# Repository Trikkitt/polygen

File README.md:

The folders are as follows:

3D Models : Contains the STL files for the casing and information about the physical assembly
  
PIC : Contains the source code and compiled .HEX file for the PIC Microcontroller used by the game

Micropython : Contains the Micropyhon code used by the ESP8285 used by the game

PCB : Contains the KiCAD PCB design used in each of the game units
  
Game : Contains the primary game code including database

Sounds: The audio files played by the game units, along with some source / raw media.

The 3D model was designed using Tinkercad.  The URL for the 2024 design is https://www.tinkercad.com/things/fUl2xMWVo1S-polygen-case-2024-final and the 2025 design https://www.tinkercad.com/things/fGMrmOF5N9D-polygen-case-2025-final and this repository contains the export STL files from Tinkercad.

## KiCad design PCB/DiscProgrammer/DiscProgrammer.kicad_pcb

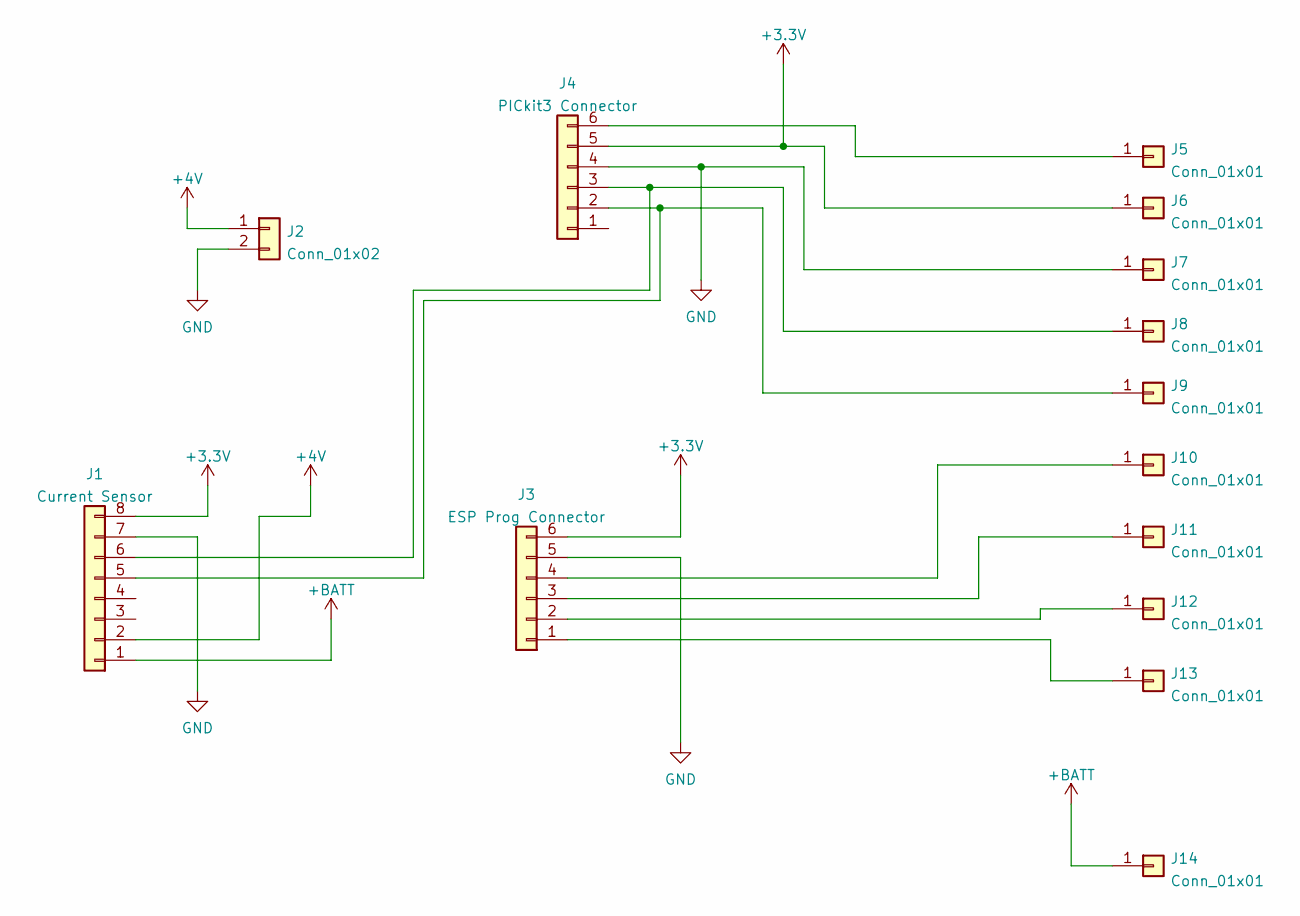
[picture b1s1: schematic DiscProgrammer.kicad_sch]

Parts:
J1: Current Sensor; PinHeader_1x08_P2.54mm_Vertical
J2: Conn_01x02; JST_PH_B2B-PH-K_1x02_P2.00mm_Vertical
J3: ESP Prog Connector; PinHeader_1x06_P2.54mm_Vertical
J4: PICkit3 Connector; PinHeader_1x06_P2.54mm_Vertical
J5, J6, J7, J8, J9, J10, J11, J12, J13, J14: Conn_01x01; Pin_D1.0mm_L10.0mm

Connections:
+3V3: J1.8, J3.6, J4.5, J6.1
+4V: J1.2, J2.1
+BATT: J1.1, J14.1
GND: J1.7, J2.2, J3.5, J4.4, J7.1
unnamed: J1.5, J4.2, J9.1
unnamed: J1.6, J4.3, J8.1
unnamed: J4.6, J5.1
unnamed: J3.4, J10.1
unnamed: J3.3, J11.1
unnamed: J3.2, J12.1
unnamed: J3.1, J13.1

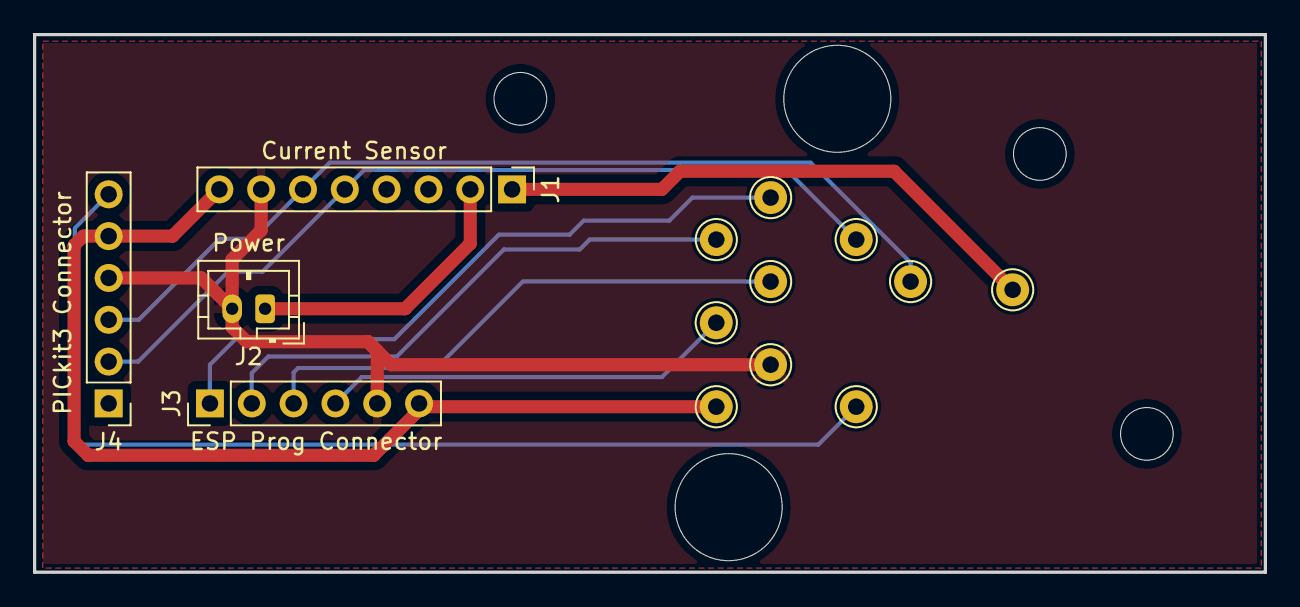
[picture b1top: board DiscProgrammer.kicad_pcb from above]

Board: 2 copper layers, 74.8 x 32.6 mm, 17 parts (0 on the bottom side), 11 nets.

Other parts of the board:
H1, H1#2: Orientation Guide 2; MountingHole_3.2mm_M3_DIN965
H2: Orientation Guide 1; MountingHole_3.2mm_M3_DIN965

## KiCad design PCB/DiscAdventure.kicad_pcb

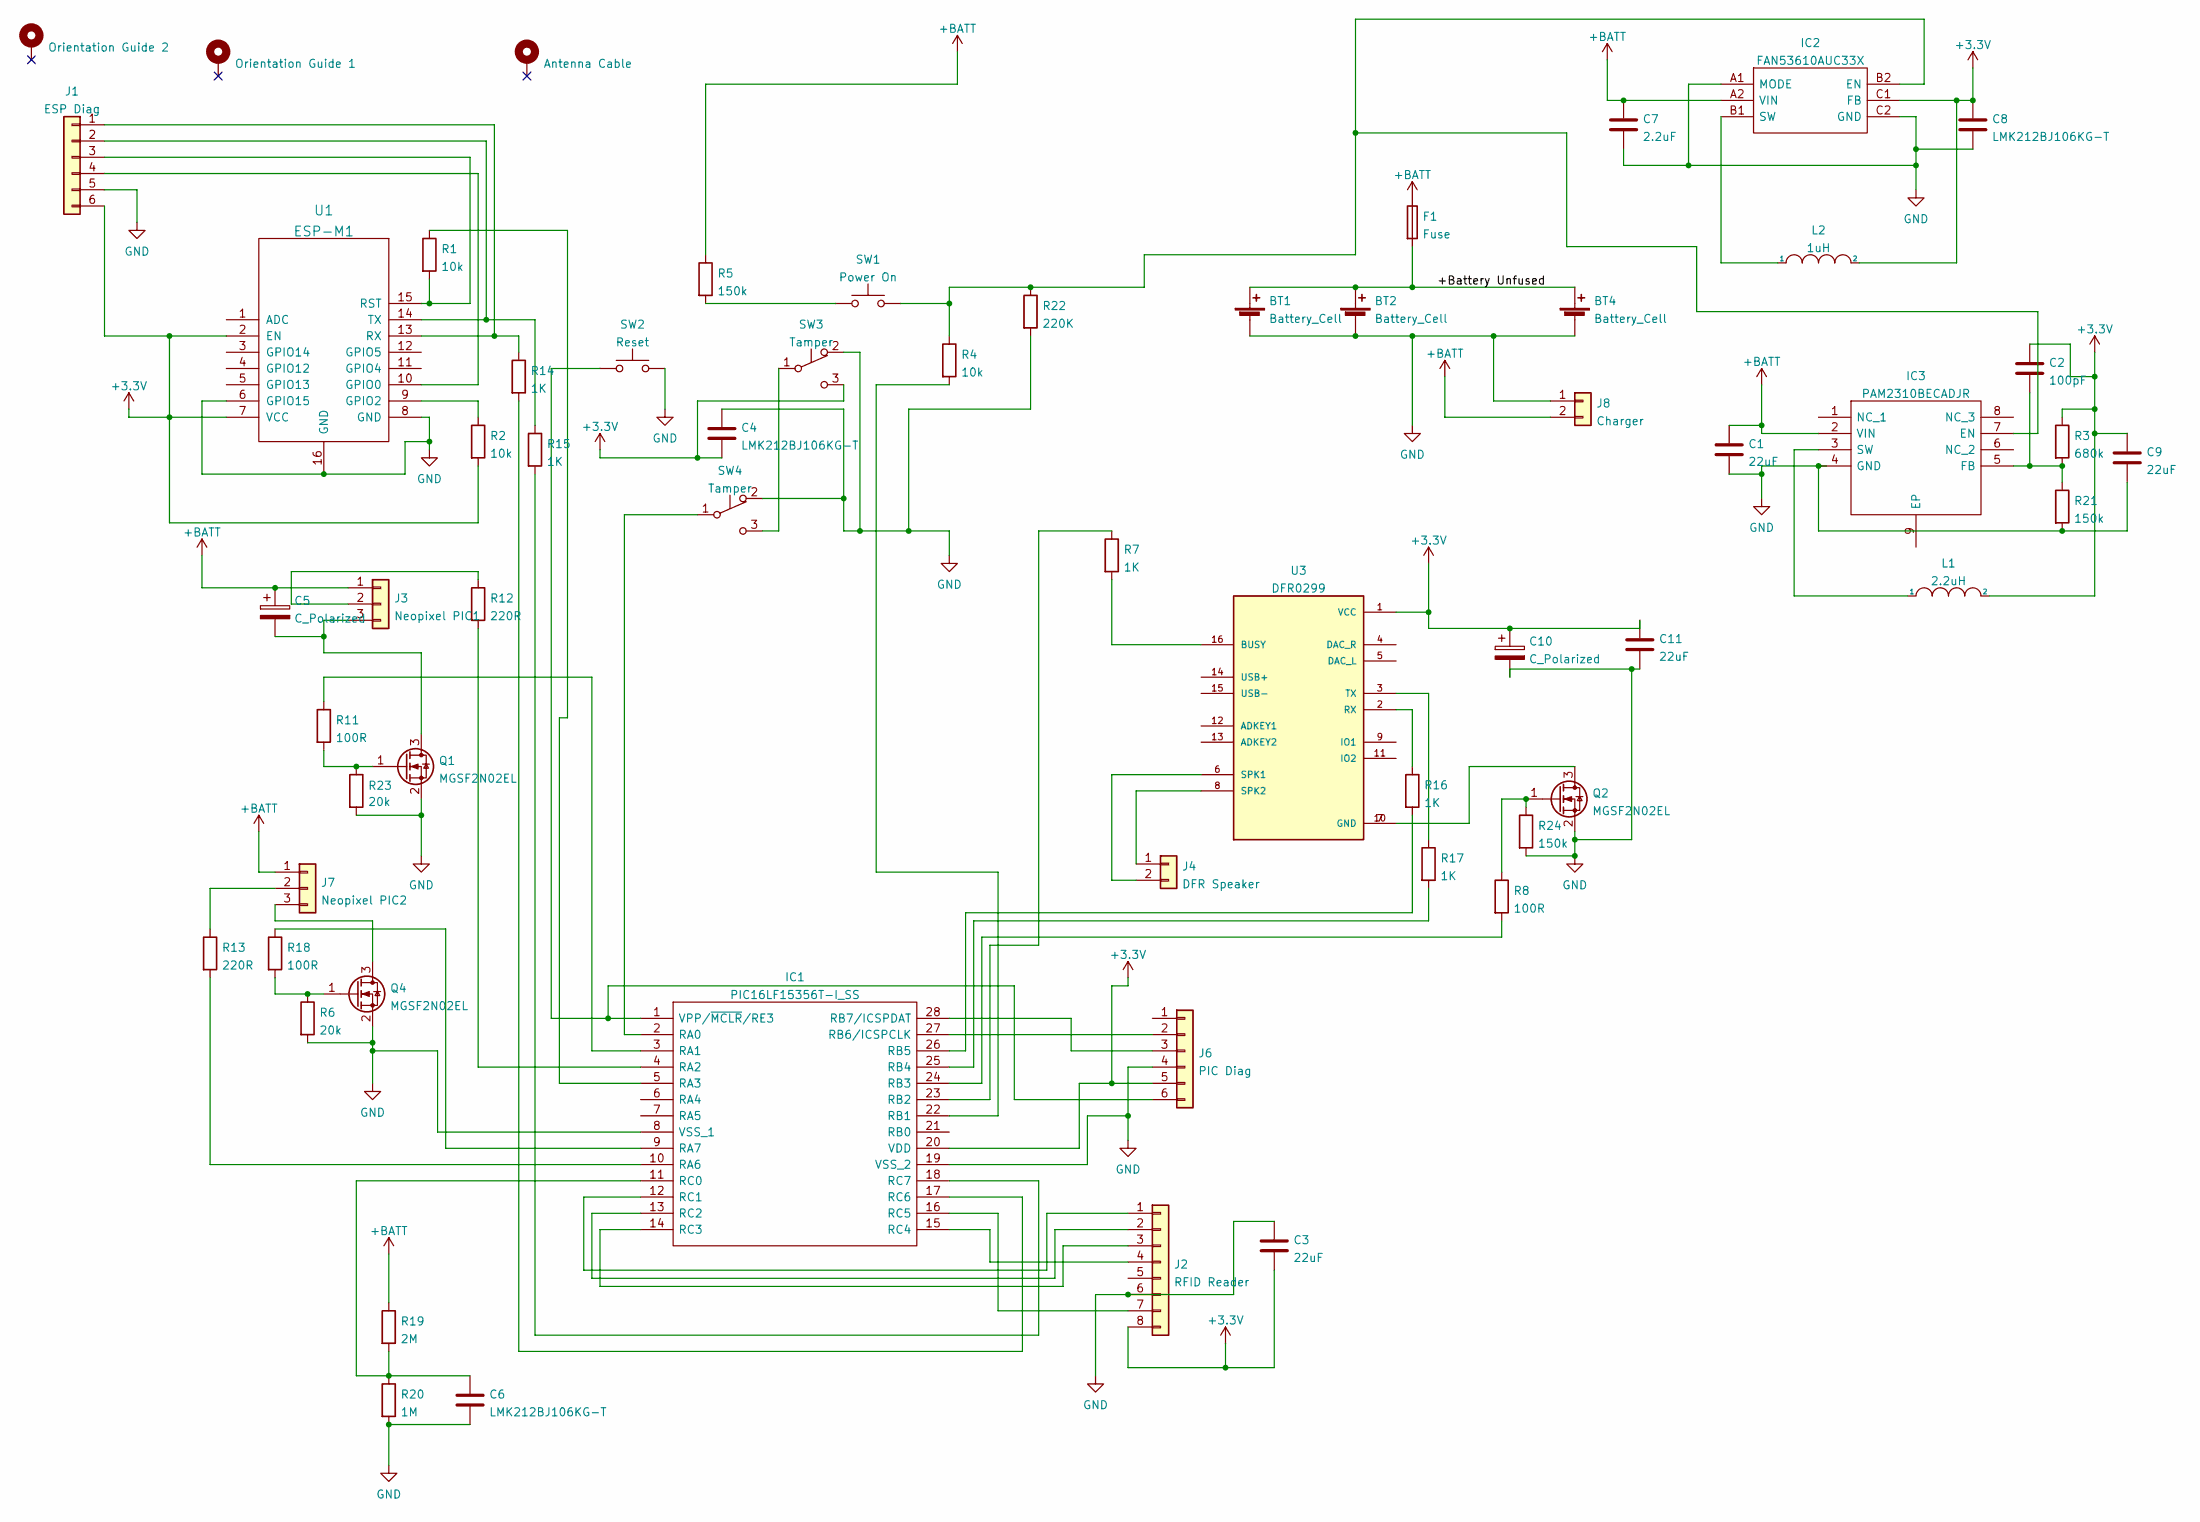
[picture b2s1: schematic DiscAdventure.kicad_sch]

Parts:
BT1, BT2, BT4: Battery_Cell; BatteryHolder_1x18650_TH
C1, C3, C9, C11: 22uF; C_0805_2012Metric
C2: 100pF; C_0805_2012Metric
C4, C6, C8: LMK212BJ106KG-T; C_0805_2012Metric
C5, C10: C_Polarized; CP_Radial_D8.0mm_P3.80mm
C7: 2.2uF; C_0805_2012Metric
F1: Fuse; Fuse_0603_1608Metric
H1: Orientation Guide 2; MountingHole_3.2mm_M3_DIN965
H2: Orientation Guide 1; MountingHole_3.2mm_M3_DIN965
H3: Antenna Cable; MountingHole_3.7mm
IC1: PIC16LF15356T-I_SS; SOIC-28W_7.5x17.9mm_P1.27mm; Mouser Part Number 579-IC16LF15356TI/SS
IC2: FAN53610AUC33X; BGA6C40P2X3_86X116X62; Mouser Part Number 512-FAN53610AUC33X
IC3: PAM2310BECADJR; SOIC127P600X163-9N; Mouser Part Number 621-PAM2310BECADJR
J1: ESP Diag; PinHeader_1x06_P2.54mm_Vertical_SMD_Pin1Left
J2: RFID Reader; PinHeader_1x08_P2.54mm_Vertical
J3: Neopixel PIC1; JST_PH_B3B-PH-K_1x03_P2.00mm_Vertical
J4: DFR Speaker; JST_PH_B2B-PH-K_1x02_P2.00mm_Vertical
J6: PIC Diag; PinHeader_1x06_P2.54mm_Vertical_SMD_Pin1Left
J7: Neopixel PIC2; JST_PH_B3B-PH-K_1x03_P2.00mm_Vertical
J8: Charger; JST_PH_B2B-PH-K_1x02_P2.00mm_Vertical
L1: 2.2uH; INDPM7466X300N
L2: 1uH; L_1008_2520Metric
Q1, Q2, Q4: MGSF2N02EL; SOT-23
R1, R2, R4: 10k; R_0603_1608Metric
R3: 680k; R_0603_1608Metric
R5, R21, R24: 150k; R_0603_1608Metric
R6, R23: 20k; R_0603_1608Metric
R7, R14, R15, R16, R17: 1K; R_0603_1608Metric
R8, R11, R18: 100R; R_0603_1608Metric
R12, R13: 220R; R_0603_1608Metric
R19: 2M; R_0603_1608Metric
R20: 1M; R_0603_1608Metric
R22: 220K; R_0603_1608Metric
SW1: Power On; SW_DIP_SPSTx01_Piano_10.8x4.1mm_W7.62mm_P2.54mm
SW2: Reset; SW_DIP_SPSTx01_Piano_10.8x4.1mm_W7.62mm_P2.54mm
SW3: Tamper; Microswitch TH
SW4: Tamper; Microswitch TH 90 Degree Right
U1: ESP-M1
U3: DFR0299; MODULE_DFR0299

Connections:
+3V3: C2.1, C3.2, C4.2, C8.1, C9.1, C10.1, C11.1, IC1.20 (VDD), IC2.C1 (FB), J1.6, J2.8, J6.5, L1.2, L2.2, R2.2, R3.1, SW3.3 (C), U1.2 (EN), U1.7 (VCC), U3.1 (VCC)
+BATT: C1.1, C5.1, C7.1, F1.1, IC2.A2 (VIN), IC3.2 (VIN), J3.1, J7.1, J8.2, R5.1, R19.1
/+Battery Unfused: BT1.1 (+), BT2.1 (+), BT4.1 (+), F1.2
GND: BT1.2 (-), BT2.2 (-), BT4.2 (-), C1.2, C3.1, C4.1, C6.2, C7.2, C8.2, C9.2, C10.2, C11.2, IC1.8 (VSS_1), IC1.19 (VSS_2), IC2.A1 (MODE), IC2.C2 (GND), IC3.4 (GND), J1.5, J2.6, J6.4, J8.1, Q1.2 (S), Q2.2 (S), Q4.2 (S), R6.2, R20.2, R21.2, R22.2, R23.2, R24.2, SW2.2, SW3.2 (A), SW4.2 (A), U1.6 (GPIO15), U1.8 (GND), U1.16 (GND)
unnamed: C2.2, IC3.5 (FB), R3.2, R21.1
unnamed: C5.2, J3.3, Q1.3 (D)
unnamed: C6.1, IC1.11 (RC0), R19.2, R20.1
unnamed: IC1.1 (VPP/~MCLR/RE3), J6.6, SW2.1
unnamed: IC1.2 (RA0), SW4.1 (B)
unnamed: IC1.3 (RA1), R11.1
unnamed: IC1.4 (RA2), R12.2
unnamed: IC1.5 (RA3), R1.1
unnamed: IC1.9 (RA7), R18.1
unnamed: IC1.10 (RA6), R13.2
unnamed: IC1.12 (RC1), J2.1
unnamed: IC1.13 (RC2), J2.2
unnamed: IC1.14 (RC3), J2.3
unnamed: IC1.15 (RC4), J2.4
unnamed: IC1.16 (RC5), J2.7
unnamed: IC1.17 (RC6), R14.2
unnamed: IC1.18 (RC7), R15.2
unnamed: IC1.22 (RB1), R4.2
unnamed: IC1.23 (RB2), R7.1
unnamed: IC1.24 (RB3), R8.2
unnamed: IC1.25 (RB4), R17.2
unnamed: IC1.26 (RB5), R16.2
unnamed: IC1.27 (RB6/ICSPCLK), J6.2
unnamed: IC1.28 (RB7/ICSPDAT), J6.3
unnamed: IC2.B1 (SW), L2.1
unnamed: IC2.B2 (EN), IC3.7 (EN), R4.1, R22.1, SW1.2
unnamed: IC3.3 (SW), L1.1
unnamed: J1.1, R14.1, U1.13 (RX)
unnamed: J1.2, R15.1, U1.14 (TX)
unnamed: J1.3, R1.2, U1.15 (RST)
unnamed: J1.4, U1.10 (GPIO0)
unnamed: J3.2, R12.1
unnamed: J4.1, U3.8 (SPK2)
unnamed: J4.2, U3.6 (SPK1)
unnamed: J7.2, R13.1
unnamed: J7.3, Q4.3 (D)
unnamed: Q1.1 (G), R11.2, R23.1
unnamed: Q2.1 (G), R8.1, R24.1
unnamed: Q2.3 (D), U3.7 (GND), U3.10 (GND)
unnamed: Q4.1 (G), R6.1, R18.2
unnamed: R2.1, U1.9 (GPIO2)
unnamed: R5.2, SW1.1
unnamed: R7.2, U3.16 (BUSY)
unnamed: R16.1, U3.2 (RX)
unnamed: R17.1, U3.3 (TX)
unnamed: SW3.1 (B), SW4.3 (C)

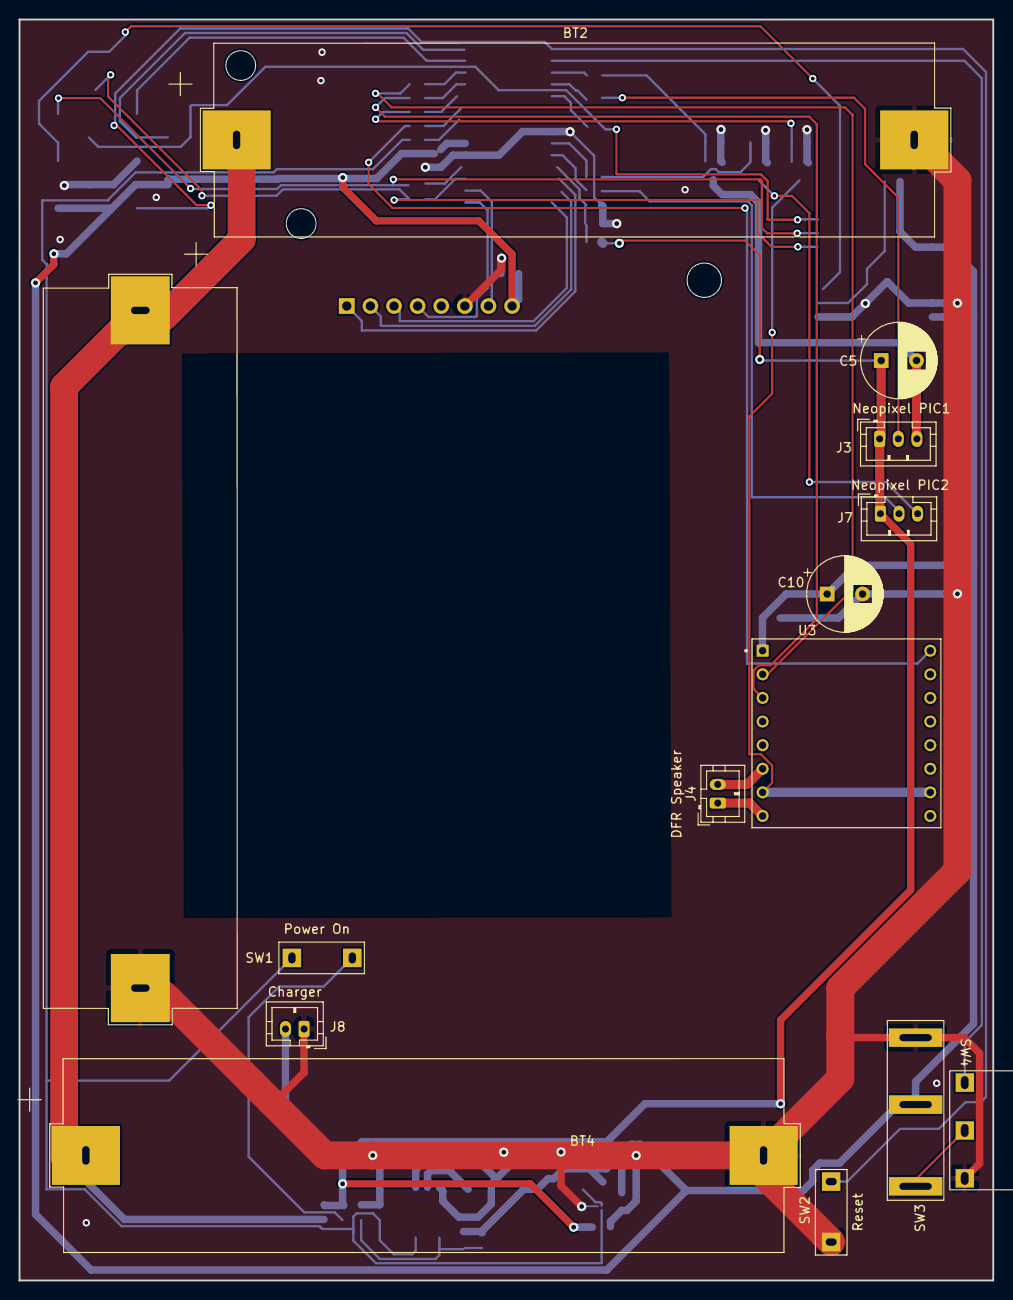
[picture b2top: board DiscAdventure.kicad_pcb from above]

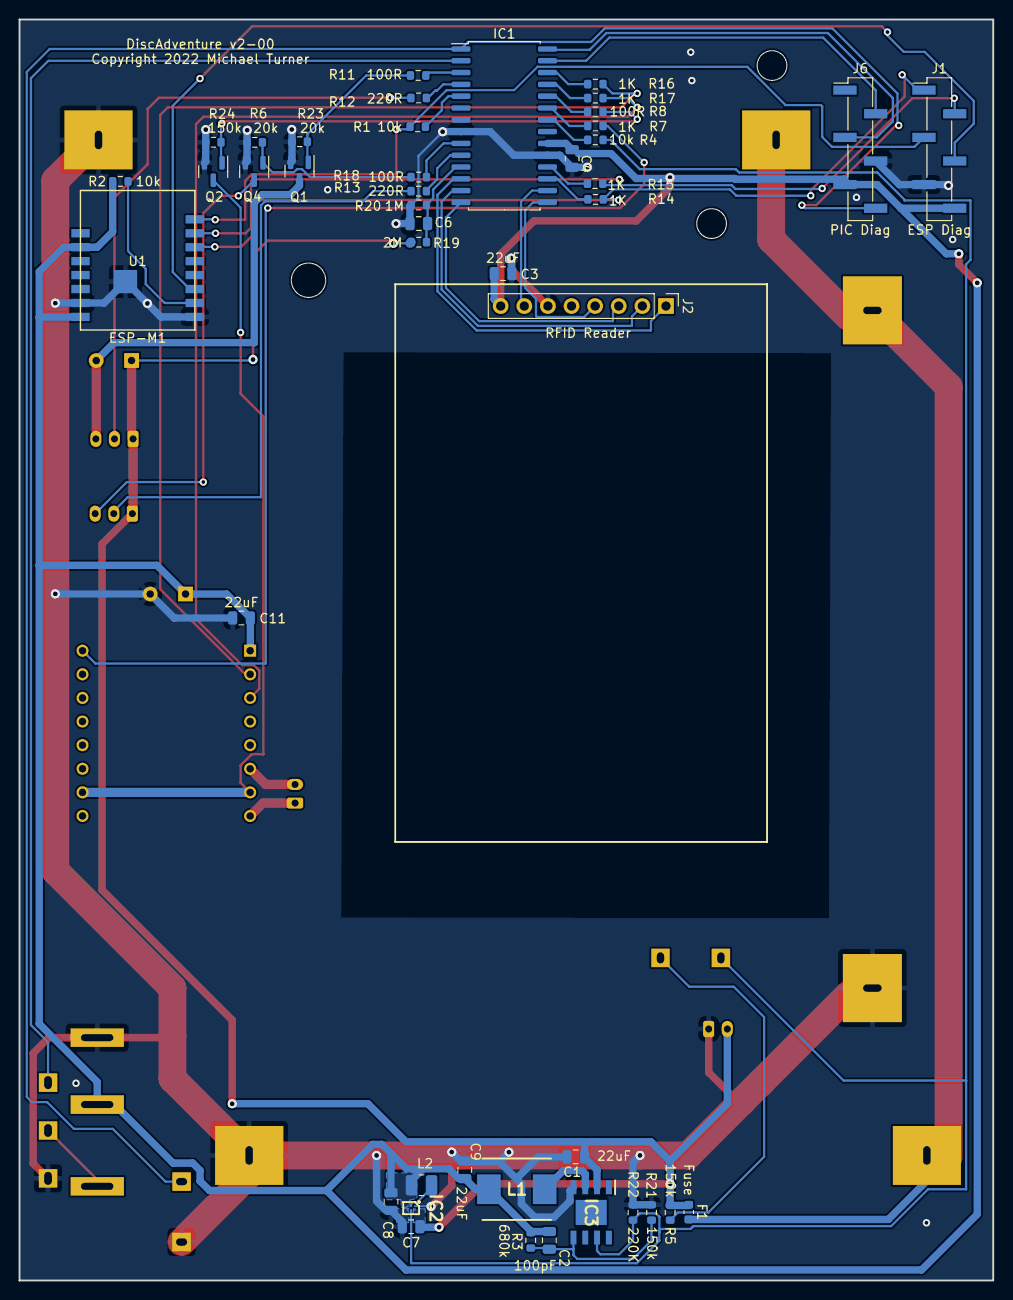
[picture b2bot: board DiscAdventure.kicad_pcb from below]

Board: 2 copper layers, 104.7 x 135.6 mm, 61 parts (44 on the bottom side), 50 nets.

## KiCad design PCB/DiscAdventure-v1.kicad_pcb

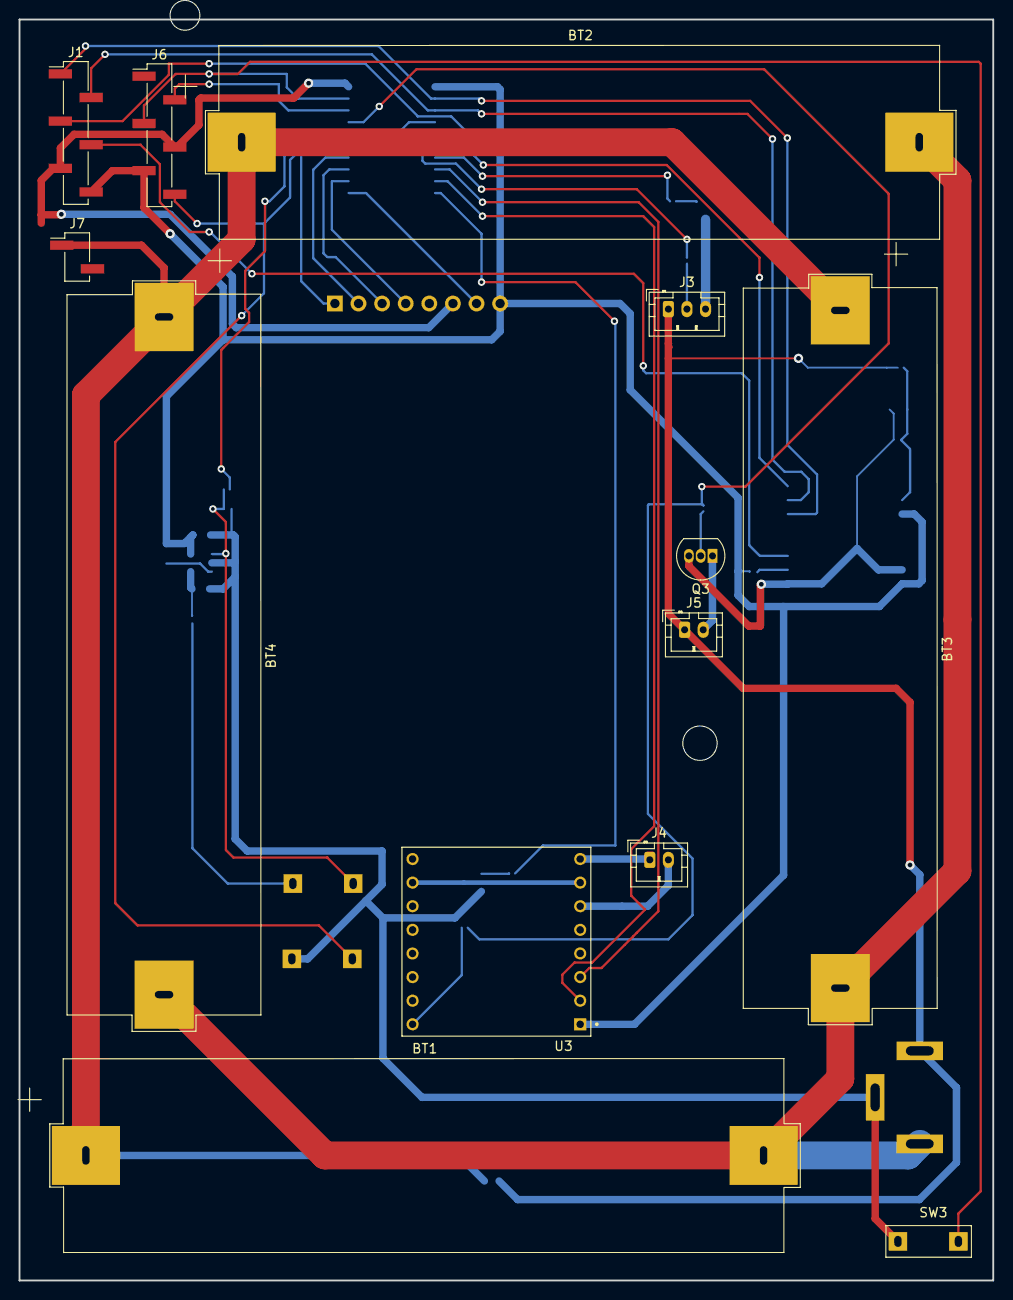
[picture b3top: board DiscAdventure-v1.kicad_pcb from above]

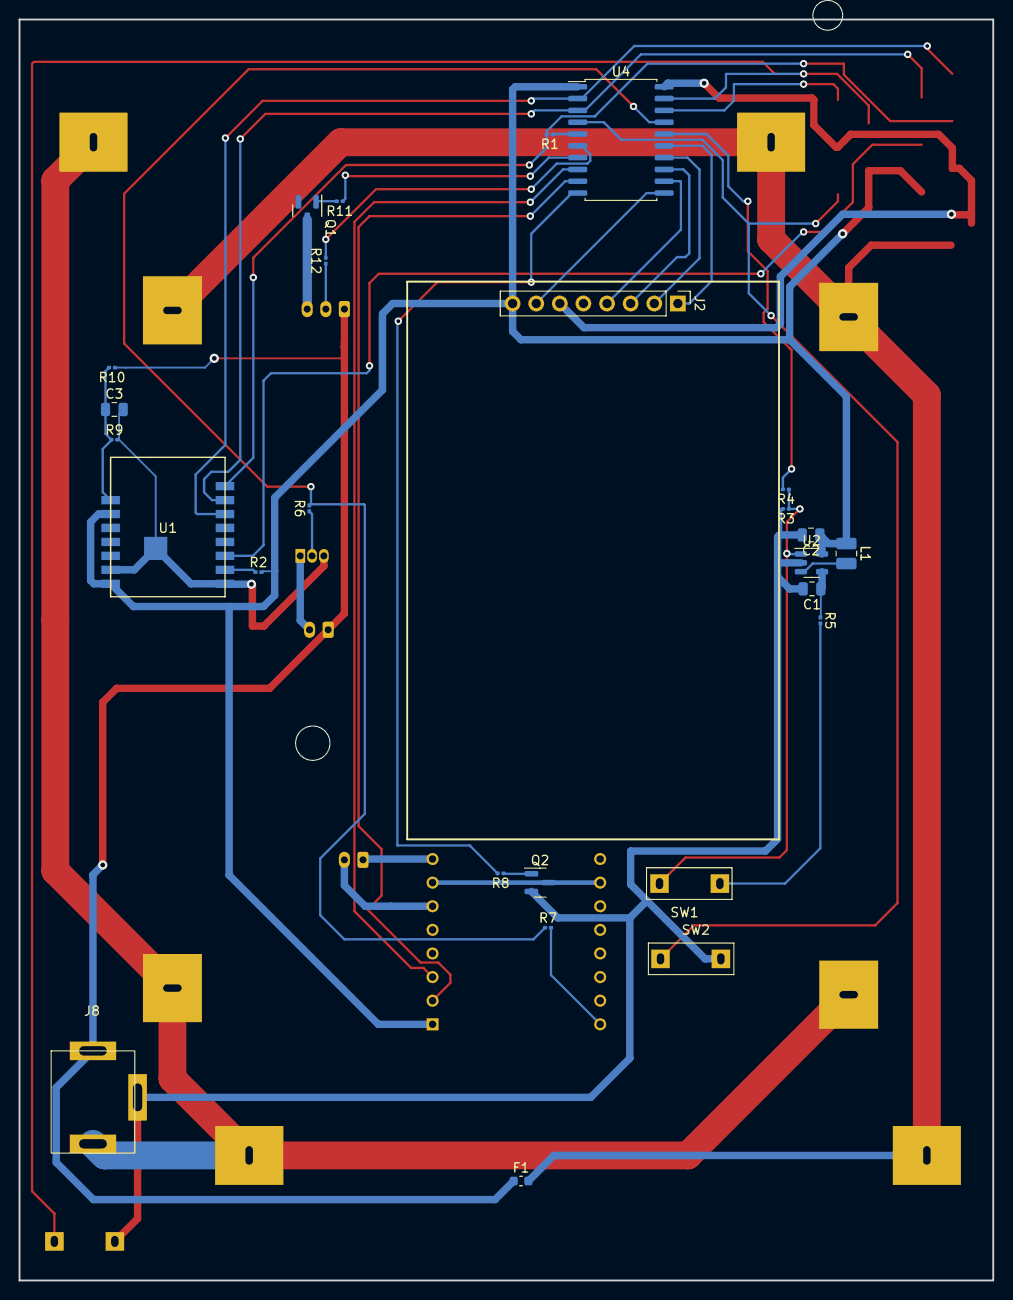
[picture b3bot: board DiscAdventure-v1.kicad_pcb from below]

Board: 2 copper layers, 104.7 x 135.6 mm, 42 parts (26 on the bottom side), 40 nets.

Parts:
BT1, BT2, BT3, BT4: Battery_Cell; BatteryHolder_1x18650_TH
C1, C2, C3: LMK212BJ106KG-T; C_0805_2012Metric
F1: Fuse; Fuse_0603_1608Metric
H1: Orientation Guide 2; MountingHole_3.2mm_M3_DIN965
H2: Orientation Guide 1; MountingHole_3.2mm_M3_DIN965
H3: Antenna Cable; MountingHole_3.7mm
J1: ESP Diag; PinHeader_1x06_P2.54mm_Vertical_SMD_Pin1Left
J2: RFID Reader; PinHeader_1x08_P2.54mm_Vertical
J3: Neopixel; JST_PH_B3B-PH-K_1x03_P2.00mm_Vertical
J4: DFR Speaker; JST_PH_B2B-PH-K_1x02_P2.00mm_Vertical
J5: PWM Speaker; JST_PH_B2B-PH-K_1x02_P2.00mm_Vertical
J6: PIC Diag; PinHeader_1x06_P2.54mm_Vertical_SMD_Pin1Left
J7: Conn_01x01; PinHeader_1x02_P2.54mm_Vertical_SMD_Pin1Left
J8: Barrel_Jack_Switch; PJ-028B Barrel Connector
L1: MAKK2520T4R7M; L_1008_2520Metric
Q1, Q2: MGSF2N02EL; SOT-23
Q3: BC549; TO-92_Inline
R1, R2, R4: 10k; R_0201_0603Metric
R3, R5: 20k; R_0201_0603Metric
R6, R12: 220R; R_0201_0603Metric
R7, R8, R11: 100R; R_0201_0603Metric
R9: 2M; R_0201_0603Metric
R10: 10M; R_0201_0603Metric
SW1: Power On; SW_DIP_SPSTx01_Piano_10.8x4.1mm_W7.62mm_P2.54mm
SW2: Reset; SW_DIP_SPSTx01_Piano_10.8x4.1mm_W7.62mm_P2.54mm
SW3: Tamper Detect; SW_DIP_SPSTx01_Piano_10.8x4.1mm_W7.62mm_P2.54mm
U1: ESP-M1
U2: PAM2301CAAB330; TSOT-23-5
U3: DFR0299; MODULE_DFR0299
U4: PIC16F15345-I/SO; SOIC-20W_7.5x12.8mm_P1.27mm

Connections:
+3V3: C2.1, J1.6, J2.8, J6.5, L1.1, R2.2, U1.2 (EN), U1.7 (VCC), U2.5 (VOUT), U3.1 (VCC), U4.1 (VDD)
+BATT: C1.1, F1.1, J3.1, J5.1, J8.1, R5.1, R10.1, U2.4 (VIN)
/+Battery Unfused: BT1.1 (+), BT2.1 (+), BT3.1 (+), BT4.1 (+), F1.2, J7.1
/-Battery Unfused: BT1.2 (-), BT2.2 (-), BT3.2 (-), BT4.2 (-), J8.2
GND: C1.2, C2.2, C3.2, J1.5, J2.6, J6.4, J8.3, Q1.2 (S), Q2.2 (S), Q3.3 (E), R3.2, R9.2, SW2.2, SW3.1, U1.6 (GPIO15), U1.8 (GND), U1.16 (GND), U2.2 (GND), U4.20 (Vss)
unnamed: C3.1, R9.1, R10.2, U1.1 (ADC)
unnamed: J1.1, U1.13 (RX), U4.2 (RA5)
unnamed: J1.2, U1.14 (TX), U4.3 (RA4)
unnamed: J1.3, R1.2, U1.15 (RST)
unnamed: J1.4, U1.10 (GPIO0)
unnamed: J2.1, U4.15 (RC1)
unnamed: J2.2, U4.14 (RC2)
unnamed: J2.3, U4.13 (RB4)
unnamed: J2.4, U4.12 (RB5)
unnamed: J2.7, U4.11 (RB6)
unnamed: J3.2, R12.1
unnamed: J3.3, Q1.3 (D)
unnamed: J4.1, U3.8 (SPK2)
unnamed: J4.2, U3.6 (SPK1)
unnamed: J5.2, Q3.1 (C)
unnamed: J6.2, U4.18 (RA1/ICSPCLK)
unnamed: J6.3, SW3.2, U4.19 (RA0/ICSPDAT)
unnamed: J6.6, SW2.1, U4.4 (Vpp/MCLR/RA3)
unnamed: L1.2, U2.3 (SW)
unnamed: Q1.1 (G), R11.2
unnamed: Q2.1 (G), R8.1
unnamed: Q2.3 (D), U3.7 (GND), U3.10 (GND)
unnamed: Q3.2 (B), R6.1
unnamed: R1.1, U4.5 (RC5)
unnamed: R2.1, U1.9 (GPIO2)
unnamed: R3.1, R4.1, SW1.2, U2.1 (EN)
unnamed: R4.2, U4.16 (RC0)
unnamed: R5.2, SW1.1
unnamed: R6.2, R7.1, U4.17 (RA2)
unnamed: R7.2, U3.16 (BUSY)
unnamed: R8.2, U4.10 (RB7)
unnamed: R11.1, U4.7 (RC3)
unnamed: R12.2, U4.6 (RC4)
unnamed: U3.2 (RX), U4.9 (RC7)
unnamed: U3.3 (TX), U4.8 (RC6)

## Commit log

2024-05-20 Added 3D model
2024-05-20 Create LICENSE
2024-05-20 Initial code publication.
2024-05-20 Added new map location calc
2026-02-17 Revise PCB Information with updates on components
    Updated PCB information to reflect component changes and availability issues.
2026-02-17 Add programmer information to programmer-info.txt
2026-02-17 Update PCB Information with tamper detection details
    Added information about optional tamper detection switches and their configuration.
2026-02-17 Updated case design to 2025 version.

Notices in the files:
PCB/DiscAdventure.kicad_pcb:
Copyright 2022 Michael Turner
